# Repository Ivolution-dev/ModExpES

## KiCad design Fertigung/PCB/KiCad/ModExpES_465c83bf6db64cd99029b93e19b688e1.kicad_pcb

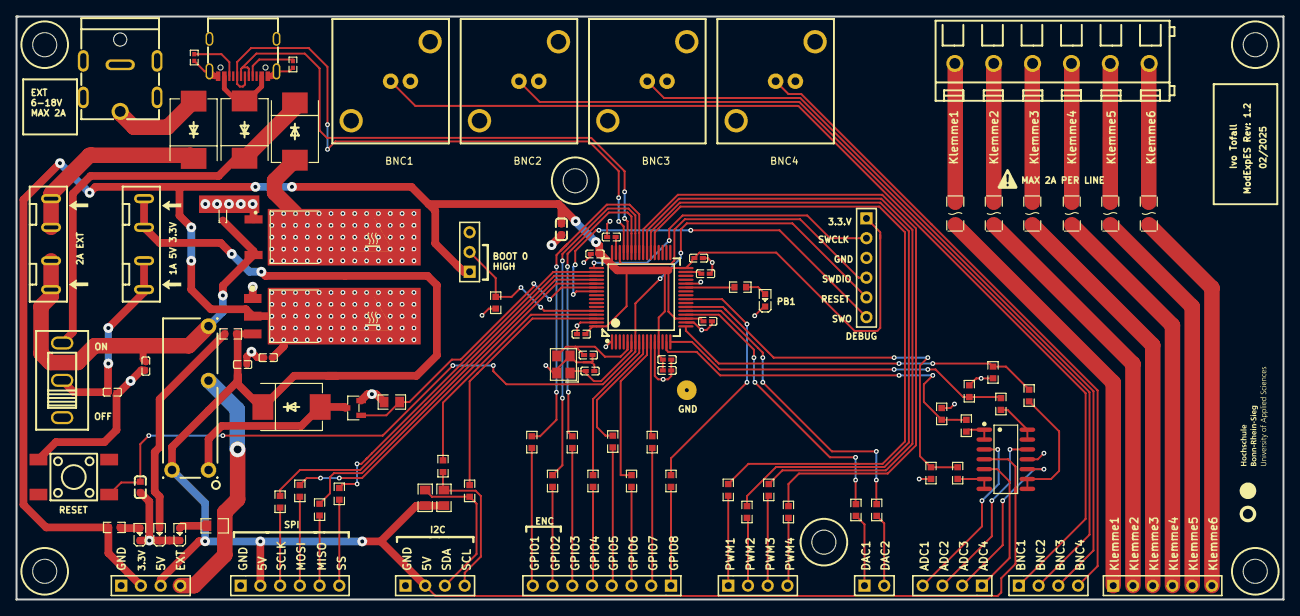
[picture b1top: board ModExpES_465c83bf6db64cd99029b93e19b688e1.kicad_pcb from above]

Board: 2 copper layers, 163.0 x 75.0 mm, 109 parts (0 on the bottom side), 99 nets.

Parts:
150Ω: 150Ω; R0603
BNC1, BNC2, BNC3, BNC4: RS PRO BNC; RS PRO BUCHSE KOAXIALSTECKVERBINDER
C1, C2, C3, C4, C16: 1uF; C0402
C5: 100nF; C0603
C6, C9, C10, C11, C15: 100nF; C0402
C7, C8: 10pF; C0402
C12: 4.7uF; C0603
C13, C14: 2.2uF; C0402
D4: ESDA18-1K; SOD-523_L1.2-W0.8-LS1.6-RD-1
F1, F2, F3, F4, F5, F6: TLC-NSMD100/24; F1206
FH1, FH2: XF-506P; FUSE-TH_XF-506P
H1, H2, H5, H8, H9: HDR-F-2.54_1x4; HDR-F-2.54_1X4
H3: HDR-F-2.54_1x8; HDR-F-2.54_1X8
H4, H6: HDR-F-2.54_1x6; HDR-F-2.54_1X6
H7: HDR-F-2.54_1x2; HDR-F-2.54_1X2
Hole_gge5985: Hole_gge5985
Hole_gge6030: Hole_gge6030
Hole_gge6336: Hole_gge6336
Hole_gge6351: Hole_gge6351
Hole_gge74702: Hole_gge74702
Hole_gge74717: Hole_gge74717
J1: HDR-M-2.54_1x6; HDR-M-2.54_1X6
J2: HDR-M-2.54_1x3; HDR-M-2.54_1X3
K1: HF46F/005-HS1; RELAYS-TH_HF46F-XX-HS1-XXX
LED1, LED2, LED3, LED4: XL-1608SURC-06; LED0603-RD_RED
Pad_gge59266: Pad_gge59266
Pad_gge61432: Pad_gge61432
Pad_gge73410: Pad_gge73410
Pad_gge221768: Pad_gge221768
Pad_gge222989: Pad_gge222989
Q1: 2N7002K_C414015; SOT-23-3_L2.9-W1.3-P1.90-LS2.4-BR
R1, R16, R17, R30: 4.7kΩ; R0805
R2, R14: 270Ω; R0603
R3, R4: 5.1kΩ; R0402
R5: 680Ω; R0603
R6, R7, R8, R9: 5.1kΩ; R0603
R10, R11, R12, R13, R15: 10kΩ; R0603
R18, R19, R20, R21, R22, R23, R24, R25, R26, R27, R28, R29, R31, R32, R33, R34, R35, R36, R37: 150Ω; R0603
SW1: SS12D10G4 071; SW-TH_SHOU-HAN_SS12D10G4
SW3: KH-6X6X5H-STM; SW-SMD_4P-L6.0-W6.0-P4.50-LS9.0-2
U1: STM32F405RGT6; LQFP-64_L10.0-W10.0-P0.50-LS12.0-BL
U2: BL8072COTR50; TO-252-2_L6.5-W6.1-P4.58-LS10.0-BR-1
U3: NCS20074DR2G; SOIC-14_L8.7-W3.9-P1.27-LS6.0-BL
U4: GT-USB-7010ASV; USB-C-SMD_G-SWITCH_GT-USB-7010ASV
U5, U7, U9, U10: SK54C_C5449119; SMC_L6.9-W5.9-LS8.0-RD
U6: BL8072COTR33; TO-252-3_L6.6-W6.1-P2.28-LS10.1-BL
U8: MX128-5.0-06P-GN01; CONN-TH_6P-P5.00_MX128-5.0-06P-GN01-CU-Y-A
U11: HX DC007B-2.0-J; DC-IN-TH_HX-DC007B-2.5
X1: 8MHz; CRYSTAL-SMD_4P-L3.2-W2.5-BL

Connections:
+3.3V: C3.2, C6.2, C9.2, C10.2, C11.2, C12.2, C15.2, C16.2, H5.2, J1.1, J2.1, Pad_gge61432.6, Pad_gge222989.6, R2.2, U1.13, U1.19, U1.32, U1.48, U1.64, U6.2, U6.4
+5V: C4.1, FH2.1, H1.2, H4.2, H5.3, K1.6, R5.1, R16.2, R17.1, U3.4, U6.3, U10.1
ADC1: R6.2, R10.1, U1.15
ADC2: R7.2, R11.1, U1.16
ADC3: R8.2, R12.1, U1.17
ADC4: R9.2, R13.1, U1.22
BNC1_4: BNC1.4, H8.1
BNC2_4: BNC2.4, H8.2
BNC3_4: BNC3.4, H8.3
BNC4_4: BNC4.4, H8.4
BOOT: J2.2, R15.1, U1.60
D+: U1.45, U4.A6, U4.B6
D-: U1.44, U4.A7, U4.B7
DAC1: R33.2, U1.20
DAC2: R32.2, U1.21
F1_1: F1.1, H6.1
F2_1: F2.1, H6.2
F3_1: F3.1, H6.3
F4_1: F4.1, H6.4
F5_1: F5.1, H6.5
F6_1: F6.1, H6.6
FH1_1: FH1.1, U5.1
FH2_2: C2.2, FH2.2, SW1.2
GND: BNC1.1, BNC1.2, BNC1.3, BNC2.1, BNC2.2, BNC2.3, BNC3.1, BNC3.2, BNC3.3, BNC4.1, BNC4.2, BNC4.3, C1.1, C2.1, C3.1, C4.2, C5.2, C6.1, C7.1, C8.1, C9.1, C10.1, C11.1, C12.1, C13.1, C14.1, C15.1, C16.1, D4.2, H1.1, H4.1, H5.1, J1.3, LED1.1, LED2.1, LED3.1, LED4.1, Q1.2, R3.1, R4.1, R10.2, R11.2, R12.2, R13.2, R15.2, R30.2, SW3.1, U1.1, U1.12, U1.18, U1.28, U1.63, U2.1, U3.11, U4.1, U4.2, U4.3, U4.4, U4.A1B12, U4.B1A12, U6.1, U11.2, U11.3, X1.2, X1.4
GPIO1: R18.2, U1.41
GPIO2: R19.2, U1.42
GPIO3: R20.2, U1.43
GPIO4: R21.2, U1.8
GPIO5: R22.2, U1.9
GPIO6: R23.2, U1.10
GPIO7: R24.2, U1.11
GPIO8: R25.2, U1.24
H1_3: H1.3, R16.1, R31.1
H1_4: 150Ω.1, H1.4, R17.2
H4_3: H4.3, R34.2
H4_4: H4.4, R35.2
H4_5: H4.5, R36.2
H4_6: H4.6, R37.2
H9_1: H9.1, U3.5
H9_2: H9.2, U3.10
H9_3: H9.3, U3.12
H9_4: H9.4, U3.3
K1_1: K1.1, Q1.3, U10.2
LED4_2: LED4.2, R14.2
MISO: R36.1, U1.52
MOSI: R35.1, U1.53
PWM1: R29.2, U1.37
PWM2: R28.2, U1.38
PWM3: R27.2, U1.39
PWM4: R26.2, U1.40
PWR-SUP: C1.2, D4.1, FH1.2, K1.3, U2.3
R1_2: LED3.2, R1.2
R2_1: LED2.2, R2.1
R5_2: LED1.2, R5.2
R18_1: H3.8, R18.1
R19_1: H3.7, R19.1
R20_1: H3.6, R20.1
R21_1: H3.5, R21.1
R22_1: H3.4, R22.1
R23_1: H3.3, R23.1
R24_1: H3.2, R24.1
R25_1: H3.1, R25.1
R26_1: H2.4, R26.1
R27_1: H2.3, R27.1
R28_1: H2.2, R28.1
R29_1: H2.1, R29.1
R32_1: H7.2, R32.1
R33_1: H7.1, R33.1
RELAIS: Q1.1, R30.1, U1.54
RESET: C5.1, J1.5, SW3.4, U1.7
SCL: 150Ω.2, U1.61
SCLK: R34.1, U1.51
SDA: R31.2, U1.62
SS: R37.1, U1.50
SUP_OUT: H5.4, K1.2, R1.1
SW1_3: SW1.3, U7.1, U9.1
SWCLK: J1.2, U1.49
SWDIO: J1.4, U1.46
SWO: J1.6, U1.55
U1_5: C7.2, U1.5, X1.3
U1_6: C8.2, U1.6, X1.1
U1_27: R14.1, U1.27
U1_31: C14.2, U1.31
U1_47: C13.2, U1.47
U2_2: Pad_gge59266.6, Pad_gge221768.6, U2.2, U7.2
U3_1: R6.1, U3.1, U3.2
U3_6: R9.1, U3.6, U3.7
U3_8: R8.1, U3.8, U3.9
U3_13: R7.1, U3.13, U3.14
U4_A5: R4.2, U4.A5
U4_B5: R3.2, U4.B5
U5_2: U5.2, U11.1
U8_1: F6.2, U8.1
U8_2: F5.2, U8.2
U8_3: F4.2, U8.3
U8_4: F3.2, U8.4
U8_5: F2.2, U8.5
U8_6: F1.2, U8.6
VBUS-USB: U4.A4B9, U4.B4A9, U9.2

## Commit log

2024-11-27 first workflow
2024-11-27 Notizen Besprechung
2024-11-27 Sortierung und Erstellung einer Struktur
2024-12-12 Meeting push
2025-01-08 Update Besprechung
2025-01-23 Datenblatt upload
2025-01-24 Zwischenpush (noch nicht alle Dokumentationen digitalisiert)
2025-01-29 Hard/Sofrwaretestts
2025-01-29 Testsoftware fertig bis auf SPI
2025-01-30 Software update,
    TODO:
    Encoder, BMP280, PWM, Relai Datei Kommentieren.
    pdf tests dokumentieren.
    pdf schaltplan doku zu ende
2025-02-06 zwischenpush
2025-02-06 Demoscript
2025-02-06 Zwischenpush endlich diese I2C Zeug fertig mit UART
    Funfact: Mein Code war vorher schon richtig, ich bin nur zu blöd gewesen den Sensor mit 5V zu versorgen und hatte den an 3.3V angeschlossen. :.)
2025-02-08 Zwischenpush Software
2025-02-19 Push für morgen
2025-02-23 Finaler Push
2025-02-24 Create LICENSE
2025-02-27 KiCad Projekt Upload
